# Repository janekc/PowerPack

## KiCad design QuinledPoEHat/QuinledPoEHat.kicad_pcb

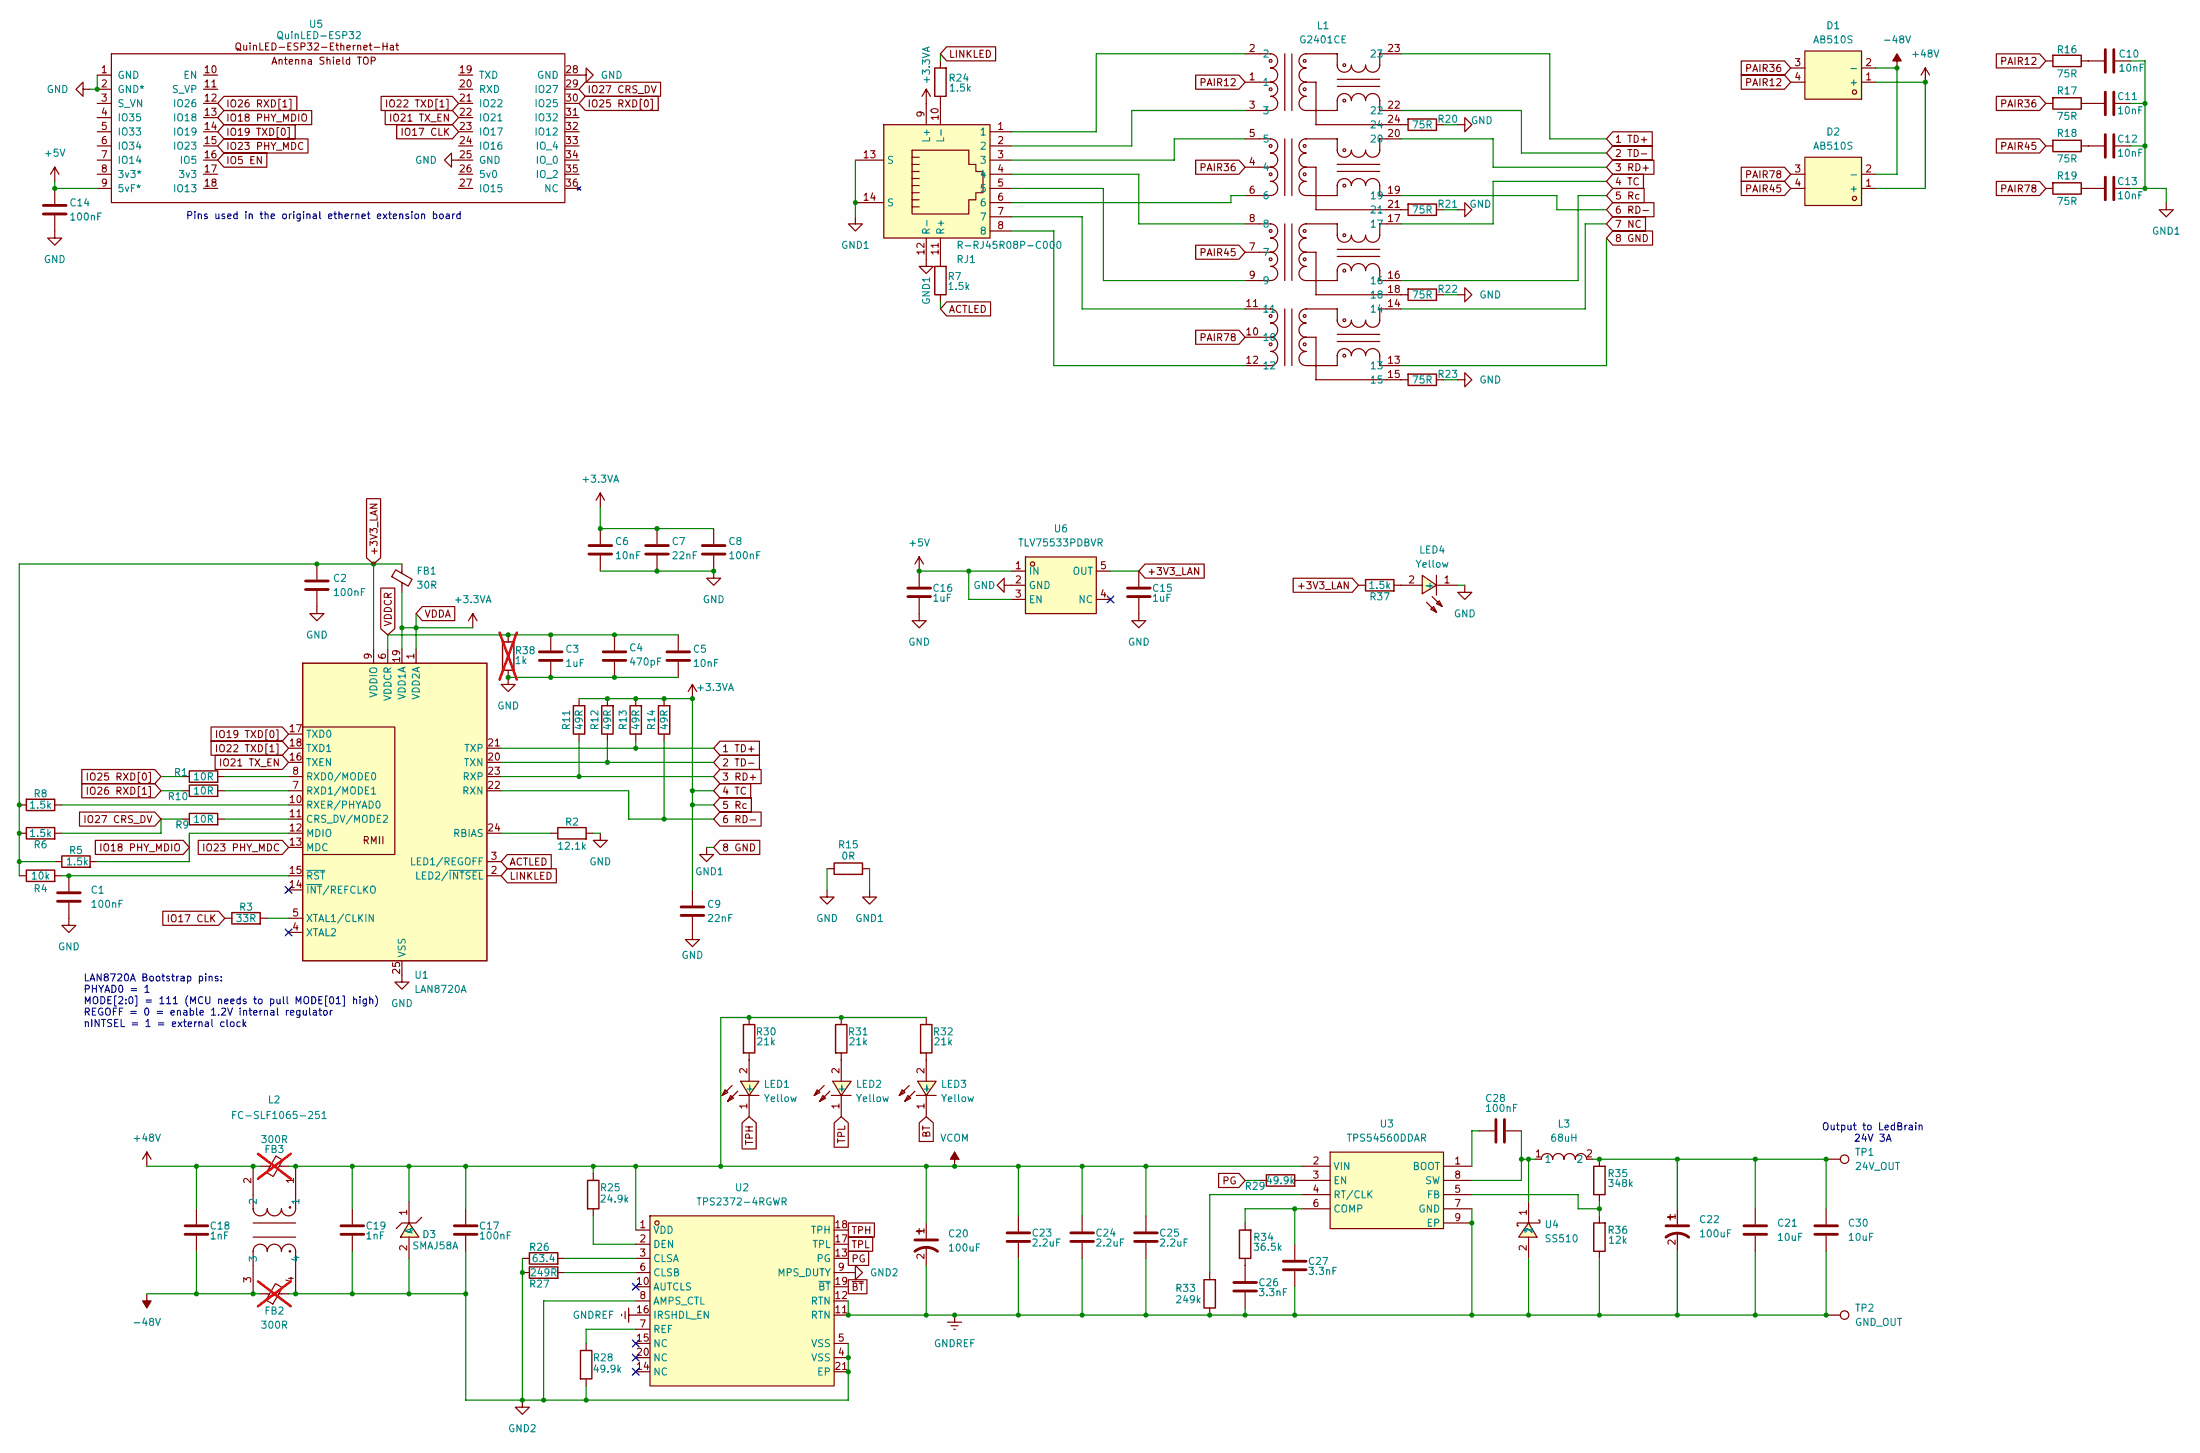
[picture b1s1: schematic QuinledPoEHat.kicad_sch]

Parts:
C1, C2, C8, C14, C17, C28: 100nF; C_0603_1608Metric_Pad1.08x0.95mm_HandSolder
C3, C15, C16: 1uF; C_0603_1608Metric_Pad1.08x0.95mm_HandSolder
C4: 470pF; C_0603_1608Metric_Pad1.08x0.95mm_HandSolder
C5, C6, C10, C11, C12, C13: 10nF; C_0603_1608Metric_Pad1.08x0.95mm_HandSolder
C7, C9: 22nF; C_0603_1608Metric_Pad1.08x0.95mm_HandSolder
C18, C19: 1nF; C_0603_1608Metric_Pad1.08x0.95mm_HandSolder
C20, C22: 100uF; CAP-SMD_BD10.0-L10.3-W10.3-FD; LCSC Part C22387799
C21, C30: 10uF; C_1206_3216Metric_Pad1.33x1.80mm_HandSolder
C23, C24, C25: 2.2uF; C_0805_2012Metric_Pad1.18x1.45mm_HandSolder
C26, C27: 3.3nF; C_0603_1608Metric_Pad1.08x0.95mm_HandSolder
D1, D2: AB510S; ABS-SMD_L5.0-W4.4-P4.00-LS7.0-BL; LCSC Part C22449614
D3: SMAJ58A; SMA_L4.3-W2.6-LS5.2-RD; LCSC Part C151246
FB1: 30R; L_0603_1608Metric_Pad1.05x0.95mm_HandSolder
FB2, FB3: 300R; L_0603_1608Metric_Pad1.05x0.95mm_HandSolder; not fitted
L1: G2401CE; SMD-24_L15.1-W7.1-P1.00-LS10.0-BL; LCSC Part C2904710
L2: FC-SLF1065-251; FILTER-SMD_L10.0-W8.7-FC-SLF1065-471; LCSC Part C5221405
L3: 68uH; IND-SMD_L11.0-W10.2_CXP1050; LCSC Part C7187328
LED1, LED2, LED3, LED4: Yellow; LED0603-RD; LCSC Part C125093
R1, R9, R10: 10R; R_0603_1608Metric_Pad0.98x0.95mm_HandSolder
R2: 12.1k; R_0603_1608Metric_Pad0.98x0.95mm_HandSolder
R3: 33R; R_0603_1608Metric_Pad0.98x0.95mm_HandSolder
R4: 10k; R_0603_1608Metric_Pad0.98x0.95mm_HandSolder
R5, R6, R7, R8, R24, R37: 1.5k; R_0603_1608Metric_Pad0.98x0.95mm_HandSolder
R11, R12, R13, R14: 49R; R_0603_1608Metric_Pad0.98x0.95mm_HandSolder
R15: 0R; R_0603_1608Metric_Pad0.98x0.95mm_HandSolder
R16, R17, R18, R19, R20, R21, R22, R23: 75R; R_0603_1608Metric_Pad0.98x0.95mm_HandSolder
R25: 24.9k; R_0603_1608Metric_Pad0.98x0.95mm_HandSolder
R26: 63.4; R_0603_1608Metric_Pad0.98x0.95mm_HandSolder
R27: 249R; R_0603_1608Metric_Pad0.98x0.95mm_HandSolder
R28, R29: 49.9k; R_0603_1608Metric_Pad0.98x0.95mm_HandSolder
R30, R31, R32: 21k; R_0603_1608Metric_Pad0.98x0.95mm_HandSolder
R33: 249k; R_0603_1608Metric_Pad0.98x0.95mm_HandSolder
R34: 36.5k; R_0603_1608Metric_Pad0.98x0.95mm_HandSolder
R35: 348k; R_0603_1608Metric_Pad0.98x0.95mm_HandSolder
R36: 12k; R_0603_1608Metric_Pad0.98x0.95mm_HandSolder
R38: 1k; R_0603_1608Metric_Pad0.98x0.95mm_HandSolder; not fitted
RJ1: R-RJ45R08P-C000; RJ45-TH_R-RJ45R08P-C000; LCSC Part C386757
TP1: 24V_OUT; TestPoint_Plated_Hole_D2.0mm
TP2: GND_OUT; TestPoint_Plated_Hole_D2.0mm
U1: LAN8720A; QFN-24_L4.0-W4.0-P0.50-BL-EP2.6; LCSC Part C45223
U2: TPS2372-4RGWR; VQFN-20_L5.0-W5.0-P0.65-BL-EP2.2; LCSC Part C470955
U3: TPS54560DDAR; SOIC-8_L5.0-W4.0-P1.27-LS6.0-BL-EP2.0; LCSC Part C31966
U4: SS510; SMB_L4.3-W3.6-LS5.3-RD; LCSC Part C908687
U5: QuinLED-ESP32; QuinLED-ESP32-Ethernet-Hat
U6: TLV75533PDBVR; SOT-23-5_L3.0-W1.7-P0.95-LS2.8-BR; LCSC Part C404027

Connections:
1 TD+: L1.23, R13.1, U1.21 (TXP)
2 TD-: L1.22, R12.1, U1.20 (TXN)
3 RD+: L1.20, R11.1, U1.23 (RXP)
4 TC: C6.1, C7.1, C8.1, C9.1, FB1.2, L1.16, L1.17, R11.2, R12.2, R13.2, R14.2, RJ1.9 (L+), U1.1 (VDD2A), U1.19 (VDD1A)
6 RD-: L1.19, R14.1, U1.22 (RXN)
7 NC: L1.14
8 GND: C10.2, C11.2, C12.2, C13.2, L1.13, R15.2, RJ1.12 (R-), RJ1.13 (S), RJ1.14 (S)
+3V3_LAN: C2.1, C15.1, FB1.1, R4.1, R5.1, R6.1, R8.2, R37.1, U1.9 (VDDIO), U6.5 (OUT)
+5V: C14.1, C16.1, U5.9 (5vF*), U6.1 (IN), U6.3 (EN)
+48V: C18.1, D1.1 (+), D2.1 (+), FB3.2, L2.2
-48V: C18.2, D1.2 (-), D2.2 (-), FB2.1, L2.3
ACTLED: R7.1, U1.3 (LED1/REGOFF)
BT: LED3.1 (-)
GND: C1.2, C2.2, C3.2, C4.2, C5.2, C6.2, C7.2, C8.2, C9.2, C14.2, C15.2, C16.2, LED4.1 (-), R2.2, R15.1, R20.1, R21.1, R22.1, R23.1, R38.1, U1.25 (VSS), U5.1 (GND), U5.2 (GND*), U5.25 (GND), U5.28 (GND), U6.2 (GND)
GND2: C17.2, C19.2, D3.2 (A), FB2.2, L2.4, R26.1, R27.1, R28.2, U2.4 (VSS), U2.5 (VSS), U2.8 (AMPS_CTL), U2.9 (MPS_DUTY), U2.21 (EP)
GNDREF: C20.2, C21.2, C22.2, C23.2, C24.2, C25.2, C26.2, C27.2, C30.2, R33.1, R36.1, TP2.1 (1_1), U2.11 (RTN), U2.12 (RTN), U2.16 (IRSHDL_EN), U3.7 (GND), U3.9 (EP), U4.2
IO17 CLK: R3.1, U5.23 (IO17)
IO18 PHY_MDIO: R5.2, U1.12 (MDIO), U5.13 (IO18)
IO19 TXD[0]: U1.17 (TXD0), U5.14 (IO19)
IO21 TX_EN: U1.16 (TXEN), U5.22 (IO21)
IO22 TXD[1]: U1.18 (TXD1), U5.21 (IO22)
IO23 PHY_MDC: U1.13 (MDC), U5.15 (IO23)
IO25 RXD[0]: R1.1, U5.30 (IO25)
IO26 RXD[1]: R10.1, U5.12 (IO26)
IO27 CRS_DV: R6.2, R9.1, U5.29 (IO27)
LINKLED: R24.2, U1.2 (LED2/~INTSEL)
unnamed: C10.1, R16.1
unnamed: C11.1, R17.1
unnamed: C12.1, R18.1
unnamed: C13.1, R19.1
unnamed: C21.1, C22.1, C30.1, L3.2, R35.2, TP1.1 (1_1)
unnamed: C26.1, R34.1
unnamed: L1.2, RJ1.1
unnamed: L1.3, RJ1.2
unnamed: L1.5, RJ1.3
unnamed: L1.6, RJ1.6
unnamed: L1.8, RJ1.4
unnamed: L1.9, RJ1.5
unnamed: L1.11, RJ1.7
unnamed: L1.12, RJ1.8
unnamed: L1.15, R23.2
unnamed: L1.18, R22.2
unnamed: L1.21, R21.2
unnamed: L1.24, R20.2
unnamed: LED1.2 (+), R30.2
unnamed: LED2.2 (+), R31.2
unnamed: LED3.2 (+), R32.2
unnamed: LED4.2 (+), R37.2
unnamed: R24.1, RJ1.10 (L-)
unnamed: R7.2, RJ1.11 (R+)
unnamed: R9.2, U1.11 (CRS_DV/MODE2)
unnamed: R2.1, U1.24 (RBIAS)
unnamed: R1.2, U1.8 (RXD0/MODE0)
unnamed: R10.2, U1.7 (RXD1/MODE1)
unnamed: R8.1, U1.10 (RXER/PHYAD0)
unnamed: R3.2, U1.5 (XTAL1/CLKIN)
unnamed: C1.1, R4.2, U1.15 (~RST)
unnamed: R26.2, U2.3 (CLSA)
unnamed: R27.2, U2.6 (CLSB)
unnamed: R25.2, U2.2 (DEN)
unnamed: R28.1, U2.7 (REF)
unnamed: C28.1, U3.1 (BOOT)
unnamed: C27.1, R34.2, U3.6 (COMP)
unnamed: R29.2, U3.3 (EN)
unnamed: R35.1, R36.2, U3.5 (FB)
unnamed: R33.2, U3.4 (RT/CLK)
unnamed: C28.2, L3.1, U3.8 (SW), U4.1
PAIR12: D1.4, L1.1, R16.2
PAIR36: D1.3, L1.4, R17.2
PAIR45: D2.4, L1.7, R18.2
PAIR78: D2.3, L1.10, R19.2
PG: R29.1, U2.13 (PG)
TPH: LED1.1 (-), U2.18 (TPH)
TPL: LED2.1 (-), U2.17 (TPL)
VCOM: C17.1, C19.1, C20.1, C23.1, C24.1, C25.1, D3.1 (C), FB3.1, L2.1, R25.1, R30.1, R31.1, R32.1, U2.1 (VDD), U3.2 (VIN)
VDDCR: C3.1, C4.1, C5.1, R38.2, U1.6 (VDDCR)
~BT: U2.19 (~BT)

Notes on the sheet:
LAN8720A Bootstrap pins: PHYAD0 = 1 MODE[2:0] = 111 (MCU needs to pull MODE[01] high) REGOFF = 0 = enable 1.2V internal regulator nINTSEL = 1 = external clock
Output to LedBrain 24V 3A
Pins used in the original ethernet extension board

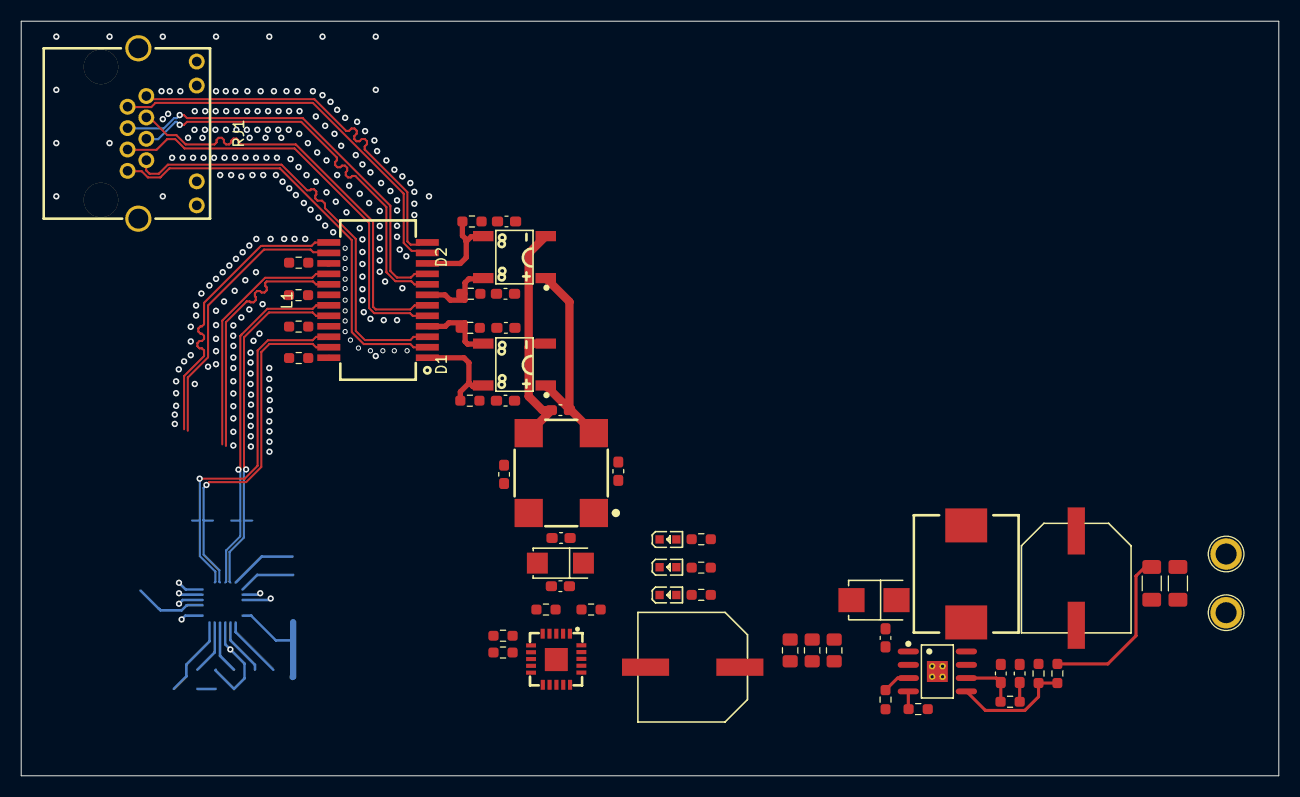
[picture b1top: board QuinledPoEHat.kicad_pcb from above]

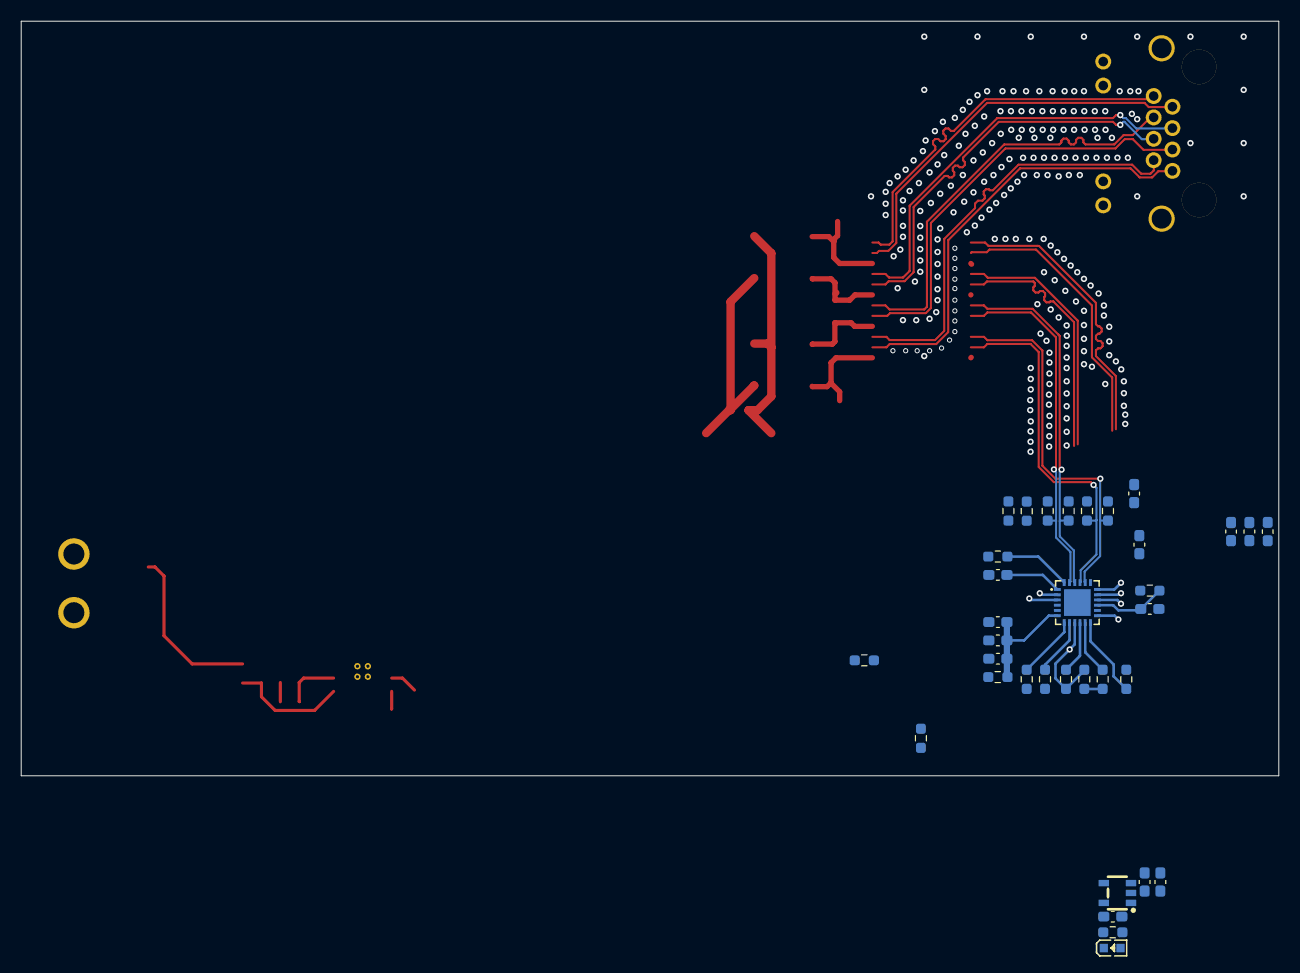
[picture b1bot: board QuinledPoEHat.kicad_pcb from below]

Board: 4 copper layers, 120.0 x 72.0 mm, 88 parts (34 on the bottom side), 67 nets.

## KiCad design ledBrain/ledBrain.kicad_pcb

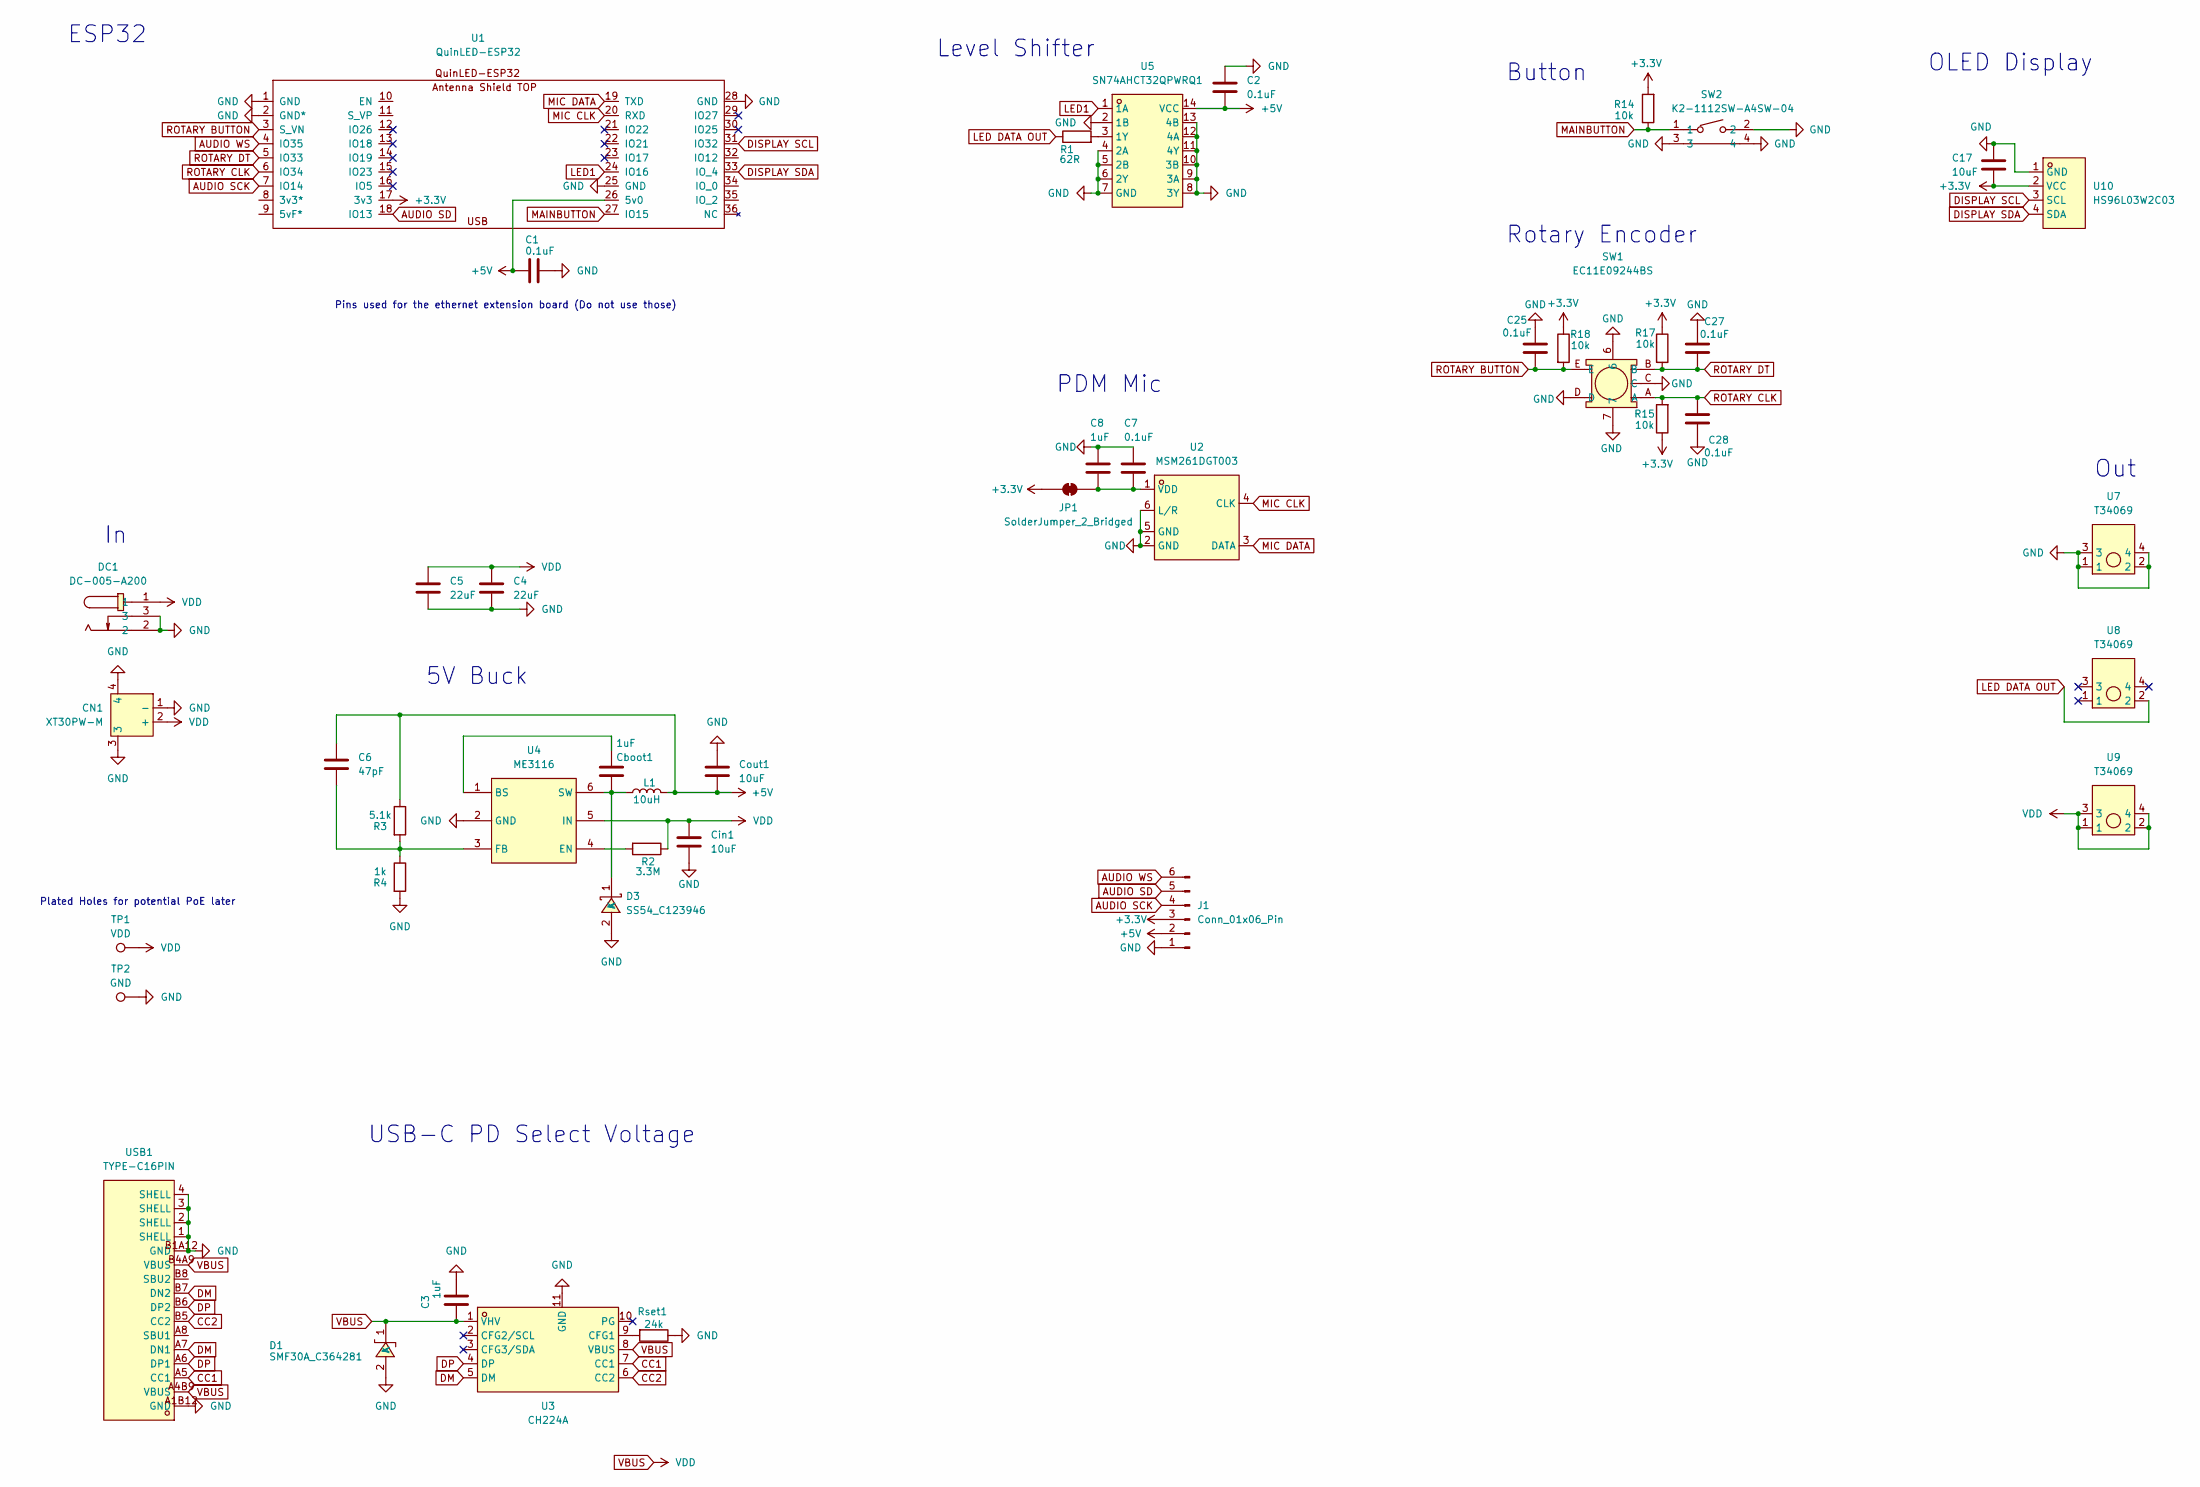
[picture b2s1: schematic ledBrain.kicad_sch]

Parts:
C1, C2, C7: 0.1uF; C_0603_1608Metric_Pad1.08x0.95mm_HandSolder
C3, C8: 1uF; C_0603_1608Metric_Pad1.08x0.95mm_HandSolder
C4, C5: 22uF; C_0805_2012Metric_Pad1.18x1.45mm_HandSolder
C6: 47pF; C_0805_2012Metric_Pad1.18x1.45mm_HandSolder
C17: 10uF; C_0805_2012Metric_Pad1.18x1.45mm_HandSolder
C25, C27, C28: 0.1uF; C_0805_2012Metric_Pad1.18x1.45mm_HandSolder
CN1: XT30PW-M; CONN-TH_XT30PW-M; LCSC Part C431092
Cboot1: 1uF; C_0805_2012Metric_Pad1.18x1.45mm_HandSolder
Cin1: 10uF; C_0805_2012Metric_Pad1.18x1.45mm_HandSolder
Cout1: 10uF; C_0805_2012Metric_Pad1.18x1.45mm_HandSolder
D1: SMF30A_C364281; SOD-123_L2.6-W1.6-LS3.5-RD; LCSC Part C364281
D3: SS54_C123946; SMA_L4.4-W2.8-LS5.4-RD; LCSC Part C123946
DC1: DC-005-A200; DC-IN-TH_DC-005-A200; LCSC Part C720557
J1: Conn_01x06_Pin; PinHeader_1x06_P2.54mm_Vertical
JP1: SolderJumper_2_Bridged; SolderJumper-2_P1.3mm_Bridged_RoundedPad1.0x1.5mm
L1: 10uH; L_APV_ANR4030
R1: 62R; R_0603_1608Metric_Pad0.98x0.95mm_HandSolder
R2: 3.3M; R_0603_1608Metric_Pad0.98x0.95mm_HandSolder
R3: 5.1k; R_0603_1608Metric_Pad0.98x0.95mm_HandSolder
R4: 1k; R_0603_1608Metric_Pad0.98x0.95mm_HandSolder
R14, R15, R17, R18: 10k; R_0603_1608Metric_Pad0.98x0.95mm_HandSolder
Rset1: 24k; R_0603_1608Metric_Pad0.98x0.95mm_HandSolder
SW1: EC11E09244BS; SW-TH_EC11XXXXXXXX; LCSC Part C470742
SW2: K2-1112SW-A4SW-04; KEY-TH_K2-1112SW-AXXW-XX; LCSC Part C223811
TP1: VDD; TestPoint_Plated_Hole_D2.0mm
TP2: GND; TestPoint_Plated_Hole_D2.0mm
U1: QuinLED-ESP32
U2: MSM261DGT003; MIC-SMD_6P-L4.0-W2.0_LMD4020T261-OC3; LCSC Part C48227730
U3: CH224A; ESSOP-10_L4.9-W3.9-P1.0-LS6.0-TL-EP; LCSC Part C42459160
U4: ME3116; SOT-23-6_L2.9-W1.6-P0.95-LS2.8-BL; LCSC Part C97643
U5: SN74AHCT32QPWRQ1; TSSOP-14_L5.0-W4.4-P0.65-LS6.5-BL; LCSC Part C507218
U7, U8, U9: T34069; XFCN_PKT-TH_4P-T34069; LCSC Part C481452
U10: HS96L03W2C03; OLED-TH_L27.8-W27.2-P2.54_C9900033791; LCSC Part C5248080
USB1: TYPE-C16PIN; USB-C-SMD_TYPE-C16PIN; LCSC Part C393939

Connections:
+3.3V: C17.1, J1.3, JP1.1 (A), R14.2, R15.1, R17.1, R18.1, U1.17 (3v3), U10.2 (VCC)
+5V: C1.1, C2.2, C6.1, Cout1.2, J1.2, L1.2, R3.1, U1.26 (5v0), U5.14 (VCC)
AUDIO SCK: J1.4, U1.7 (IO14)
AUDIO SD: J1.5, U1.18 (IO13)
AUDIO WS: J1.6, U1.4 (IO35)
CC1: U3.7 (CC1), USB1.A5 (CC1)
CC2: U3.6 (CC2), USB1.B5 (CC2)
DISPLAY SCL: U1.31 (IO32), U10.3 (SCL)
DISPLAY SDA: U1.33 (IO_4), U10.4 (SDA)
DM: U3.5 (DM), USB1.A7 (DN1), USB1.B7 (DN2)
DP: U3.4 (DP), USB1.A6 (DP1), USB1.B6 (DP2)
GND: C1.2, C2.1, C3.2, C4.2, C5.2, C7.1, C8.1, C17.2, C25.2, C27.2, C28.2, CN1.1 (-), CN1.3, CN1.4, Cin1.2, Cout1.1, D1.2 (A), D3.2 (A), DC1.2, DC1.3, J1.1, R4.2, Rset1.1, SW1.6, SW1.7, SW1.C, SW1.D, SW2.2, SW2.3, SW2.4, TP2.1 (1_1), U1.1 (GND), U1.2 (GND*), U1.25 (GND), U1.28 (GND), U2.2 (GND), U2.5 (GND), U2.6 (L/R), U3.11 (GND), U4.2 (GND), U5.2 (1B), U5.4 (2A), U5.5 (2B), U5.6 (2Y), U5.7 (GND), U5.8 (3Y), U5.9 (3A), U5.10 (3B), U5.11 (4Y), U5.12 (4A), U5.13 (4B), U7.1, U7.2, U7.3, U7.4, U10.1 (GND), USB1.1 (SHELL), USB1.2 (SHELL), USB1.3 (SHELL), USB1.4 (SHELL), USB1.A1B12 (GND), USB1.B1A12 (GND)
LED1: U1.24 (IO16), U5.1 (1A)
LED DATA OUT: R1.1, U8.2 (2_2)
MAINBUTTON: R14.1, SW2.1, U1.27 (IO15)
MIC CLK: U1.20 (RXD), U2.4 (CLK)
MIC DATA: U1.19 (TXD), U2.3 (DATA)
unnamed: Cboot1.2, D3.1 (K), L1.1, U4.6 (SW)
unnamed: C7.2, C8.2, JP1.2 (B), U2.1 (VDD)
unnamed: Rset1.2, U3.9 (CFG1)
unnamed: Cboot1.1, U4.1 (BS)
unnamed: R2.2, U4.4 (EN)
unnamed: C6.2, R3.2, R4.1, U4.3 (FB)
unnamed: R1.2, U5.3 (1Y)
ROTARY BUTTON: C25.1, R18.2, SW1.E, U1.3 (S_VN)
ROTARY CLK: C28.1, R15.2, SW1.A, U1.6 (IO34)
ROTARY DT: C27.1, R17.2, SW1.B, U1.5 (IO33)
VBUS: C3.1, C4.1, C5.1, CN1.2 (+), Cin1.1, D1.1 (K), DC1.1, R2.1, TP1.1 (1_1), U3.1 (VHV), U3.8 (VBUS), U4.5 (IN), U9.1, U9.2, U9.3, U9.4, USB1.A4B9 (VBUS), USB1.B4A9 (VBUS)

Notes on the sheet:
ESP32
5V Buck
Button
Rotary Encoder
Level Shifter
OLED Display
PDM Mic
Out
Plated Holes for potential PoE later
Pins used for the ethernet extension board (Do not use those)
USB-C PD Select Voltage

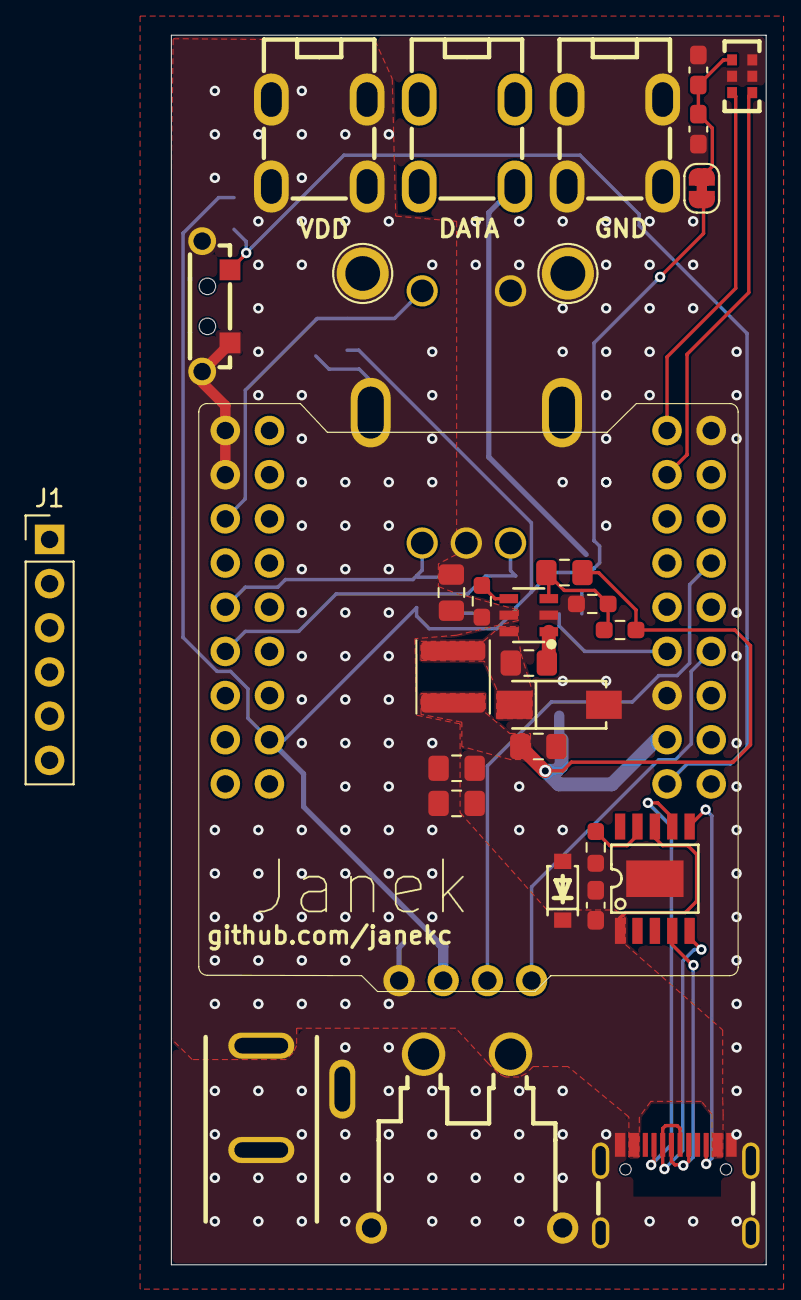
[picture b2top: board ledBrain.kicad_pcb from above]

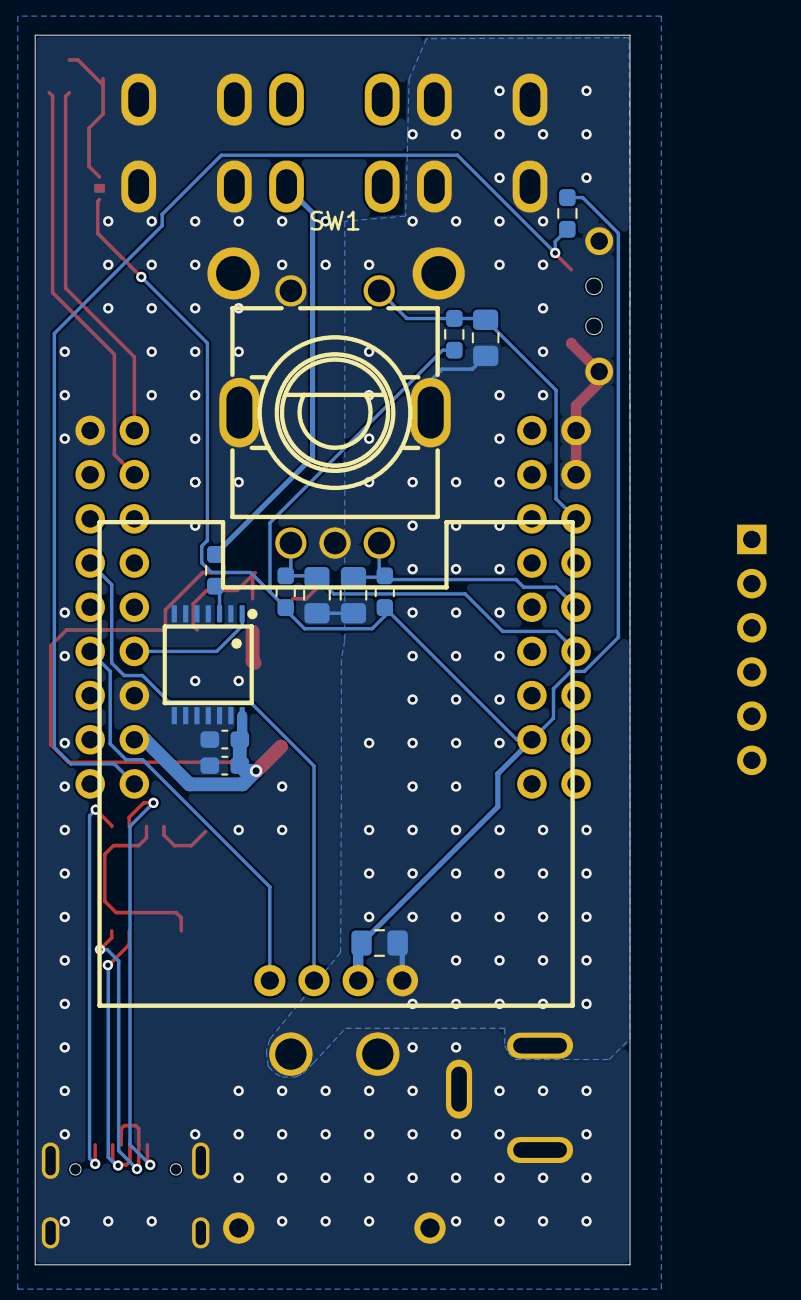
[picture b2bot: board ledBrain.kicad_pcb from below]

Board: 4 copper layers, 34.2 x 70.7 mm, 45 parts (14 on the bottom side), 28 nets.

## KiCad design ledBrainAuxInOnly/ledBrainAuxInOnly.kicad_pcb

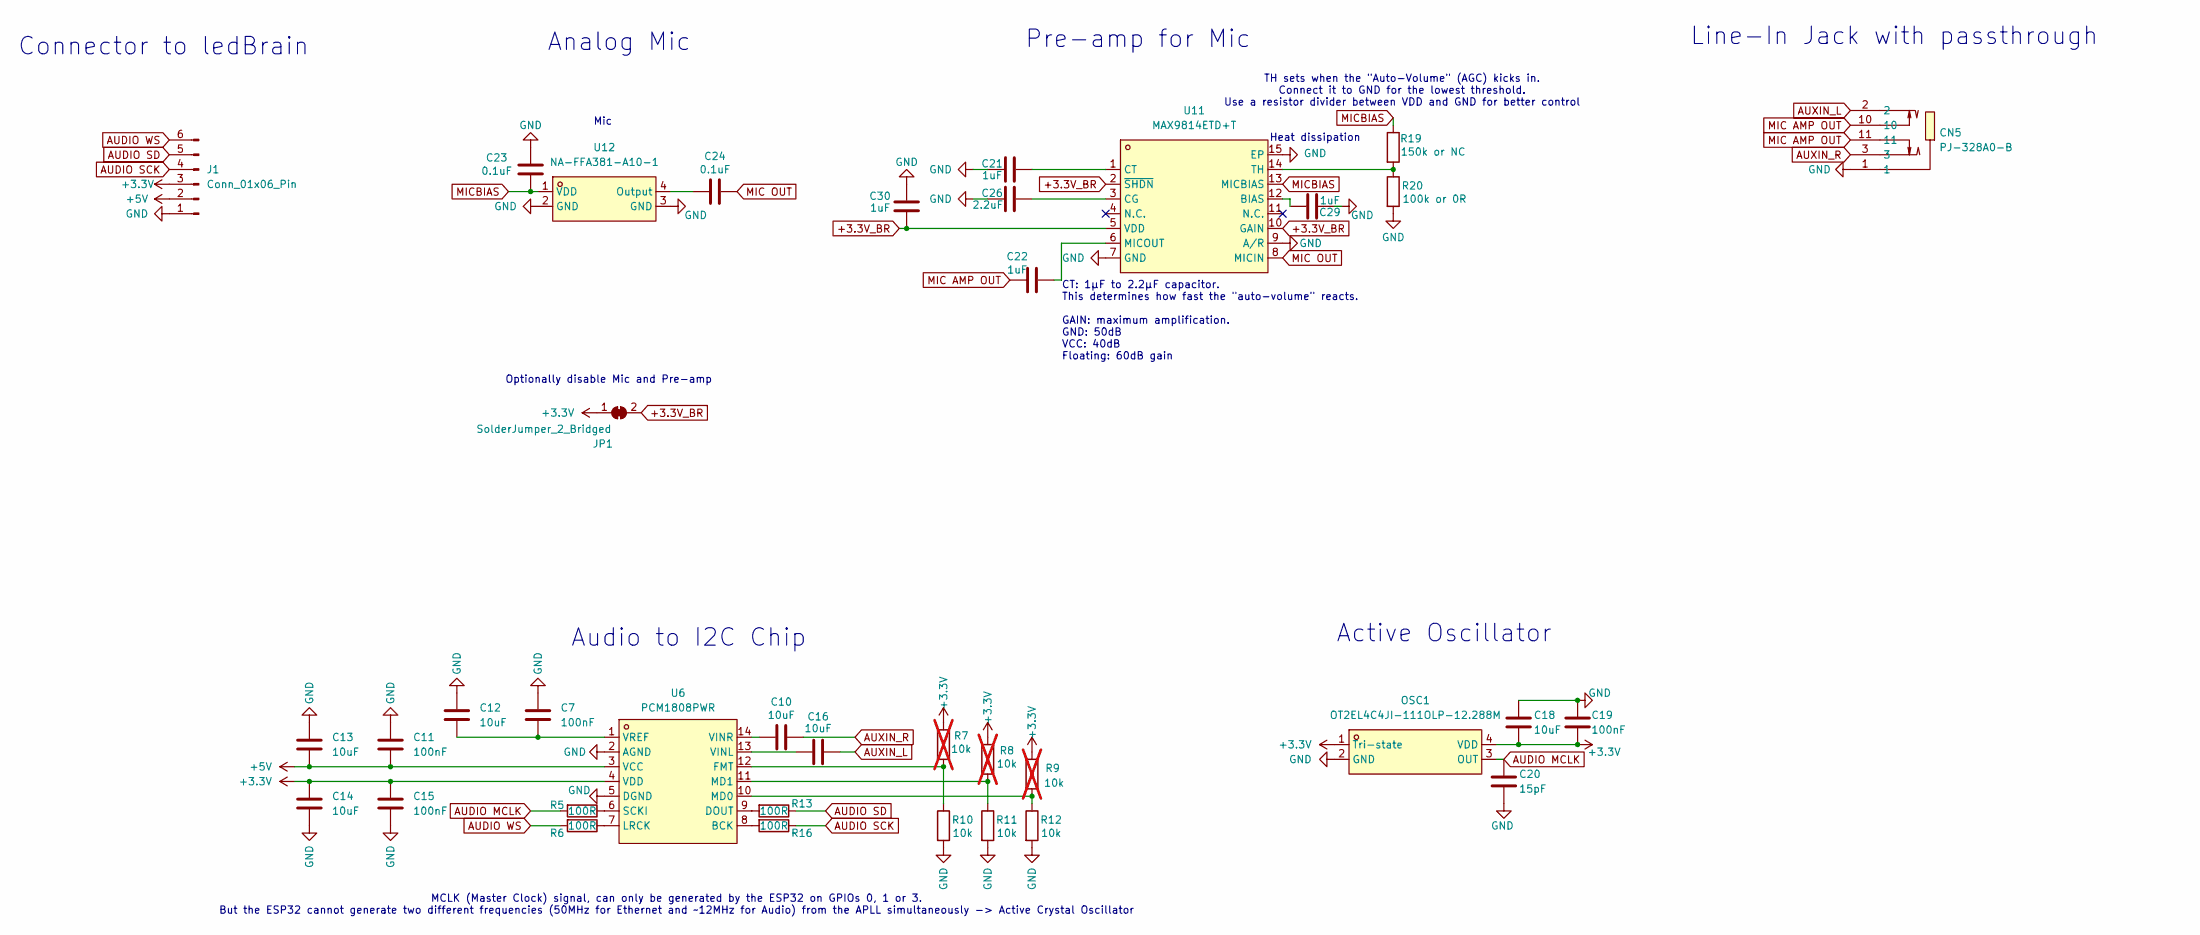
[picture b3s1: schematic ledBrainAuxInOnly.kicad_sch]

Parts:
C7, C11, C15, C19: 100nF; C_0805_2012Metric_Pad1.18x1.45mm_HandSolder
C10, C12, C13, C14, C16, C18: 10uF; C_0805_2012Metric_Pad1.18x1.45mm_HandSolder
C20: 15pF; C_0805_2012Metric_Pad1.18x1.45mm_HandSolder
C21, C22, C29, C30: 1uF; C_0805_2012Metric_Pad1.18x1.45mm_HandSolder
C23, C24: 0.1uF; C_0805_2012Metric_Pad1.18x1.45mm_HandSolder
C26: 2.2uF; C_0805_2012Metric_Pad1.18x1.45mm_HandSolder
CN5: PJ-328A0-B; AUDIO-TH_PJ-328A0-B; LCSC Part C381129
J1: Conn_01x06_Pin; PinHeader_1x06_P2.54mm_Vertical
JP1: SolderJumper_2_Bridged; SolderJumper-2_P1.3mm_Bridged_RoundedPad1.0x1.5mm
OSC1: OT2EL4C4JI-111OLP-12.288M; OSC-SMD_4P-L3.2-W2.5-BL; LCSC Part C5203546
R5, R6, R13, R16: 100R; R_0603_1608Metric_Pad0.98x0.95mm_HandSolder
R7, R8, R9: 10k; R_0603_1608Metric_Pad0.98x0.95mm_HandSolder; not fitted
R10, R11, R12: 10k; R_0603_1608Metric_Pad0.98x0.95mm_HandSolder
R19: 150k or NC; R_0603_1608Metric_Pad0.98x0.95mm_HandSolder
R20: 100k or 0R; R_0603_1608Metric_Pad0.98x0.95mm_HandSolder
U6: PCM1808PWR; TSSOP-14_L5.0-W4.4-P0.65-LS6.4-BL; LCSC Part C55513
U11: MAX9814ETD+T; TDFN-14_L3.0-W3.0-P0.40-BL-EP; LCSC Part C41714
U12: NA-FFA381-A10-1; MIC-SMD_4P-L2.8-W1.9_NA-FFA381-A10-1; LCSC Part C50275774

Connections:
+3.3V: C14.2, C15.2, C18.1, C19.1, J1.3, JP1.1 (A), OSC1.1 (Tri-state), OSC1.4 (VDD), R7.1, R8.1, R9.1, U6.4 (VDD)
+3.3V_BR: C30.1, JP1.2 (B), U11.2 (~SHDN), U11.5 (VDD), U11.10 (GAIN)
+5V: C11.1, C13.1, J1.2, U6.3 (VCC)
AUDIO MCLK: C20.2, OSC1.3 (OUT), R5.2
AUDIO SCK: J1.4, R16.1
AUDIO SD: J1.5, R13.1
AUDIO WS: J1.6, R6.2
AUXIN_L: C16.1, CN5.2
AUXIN_R: C10.1, CN5.3
GND: C7.2, C11.2, C12.2, C13.2, C14.1, C15.1, C18.2, C19.2, C20.1, C21.2, C23.1, C26.2, C29.2, C30.2, CN5.1, J1.1, OSC1.2 (GND), R10.2, R11.2, R12.2, R20.2, U6.2 (AGND), U6.5 (DGND), U11.7 (GND), U11.9 (A/R), U11.15 (EP), U12.2 (GND), U12.3 (GND)
MIC AMP OUT: C22.2, CN5.10, CN5.11
MIC OUT: C24.2, U11.8 (MICIN)
MICBIAS: C23.2, R19.1, U11.13 (MICBIAS), U12.1 (VDD)
unnamed: R16.2, U6.8 (BCK)
unnamed: R13.2, U6.9 (DOUT)
unnamed: R7.2, R10.1, U6.12 (FMT)
unnamed: R6.1, U6.7 (LRCK)
unnamed: R9.2, R12.1, U6.10 (MD0)
unnamed: R8.2, R11.1, U6.11 (MD1)
unnamed: R5.1, U6.6 (SCKI)
unnamed: C16.2, U6.13 (VINL)
unnamed: C10.2, U6.14 (VINR)
unnamed: C7.1, C12.1, U6.1 (VREF)
unnamed: C29.1, U11.12 (BIAS)
unnamed: C26.1, U11.3 (CG)
unnamed: C21.1, U11.1 (CT)
unnamed: C22.1, U11.6 (MICOUT)
unnamed: R19.2, R20.1, U11.14 (TH)
unnamed: C24.1, U12.4 (Output)

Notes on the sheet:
Connector to ledBrain
MCLK (Master Clock) signal, can only be generated by the ESP32 on GPIOs 0, 1 or 3. But the ESP32 cannot generate two different frequencies (50MHz for Ethernet and ~12MHz for Audio) from the APLL simultaneously -> Active Crystal Oscillator
Optionally disable Mic and Pre-amp
Audio to I2C Chip
Active Oscillator
Pre-amp for Mic
TH sets when the "Auto-Volume" (AGC) kicks in. Connect it to GND for the lowest threshold. Use a resistor divider between VDD and GND for better control
Line-In Jack with passthrough
Analog Mic
Mic
Heat dissipation
CT: 1µF to 2.2µF capacitor. This determines how fast the "auto-volume" reacts. GAIN: maximum amplification. GND: 50dB VCC: 40dB Floating: 60dB gain

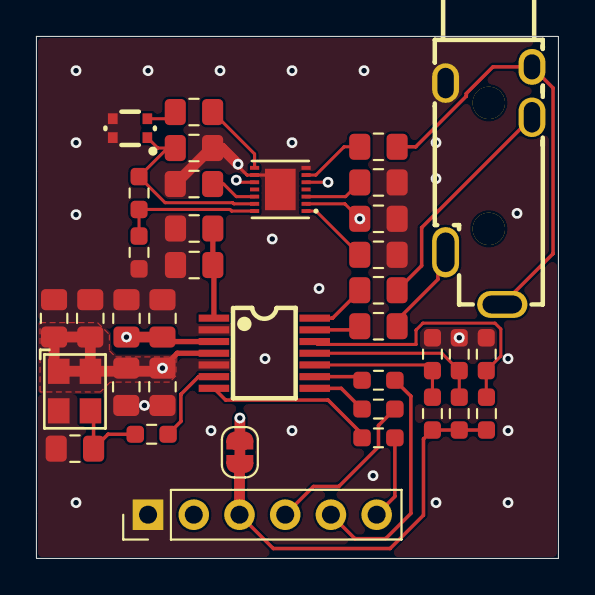
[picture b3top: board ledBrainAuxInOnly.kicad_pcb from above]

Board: 4 copper layers, 29.0 x 29.0 mm, 37 parts (0 on the bottom side), 29 nets.

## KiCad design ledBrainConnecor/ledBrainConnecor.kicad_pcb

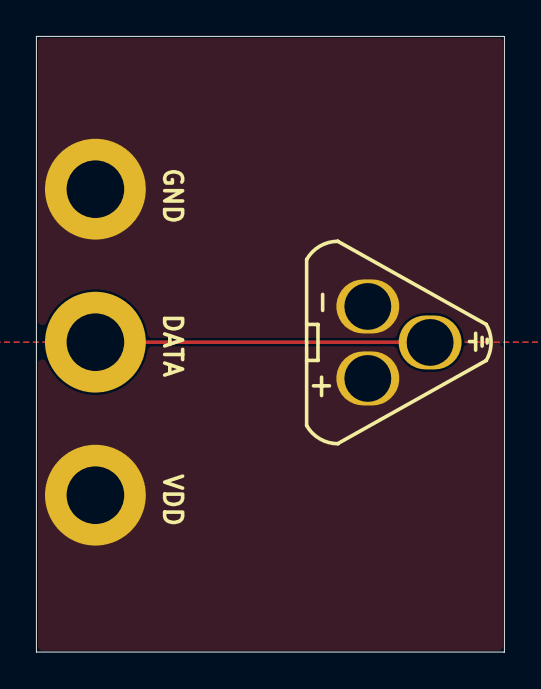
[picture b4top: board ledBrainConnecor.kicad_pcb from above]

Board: 2 copper layers, 26.0 x 34.2 mm, 4 parts (0 on the bottom side), 3 nets.

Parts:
H1: GND; MountingHole_3.2mm_M3_DIN965_Pad
H2: LED DATA OUT; MountingHole_3.2mm_M3_DIN965_Pad
H3: VDD; MountingHole_3.2mm_M3_DIN965_Pad
U4: MT30-F; CONN-TH_MT30-M

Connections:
GND: H1.1 (1_1), U4.1
LED DATA OUT: H2.1 (1_1), U4.2
VDD: H3.1 (1_1), U4.3
